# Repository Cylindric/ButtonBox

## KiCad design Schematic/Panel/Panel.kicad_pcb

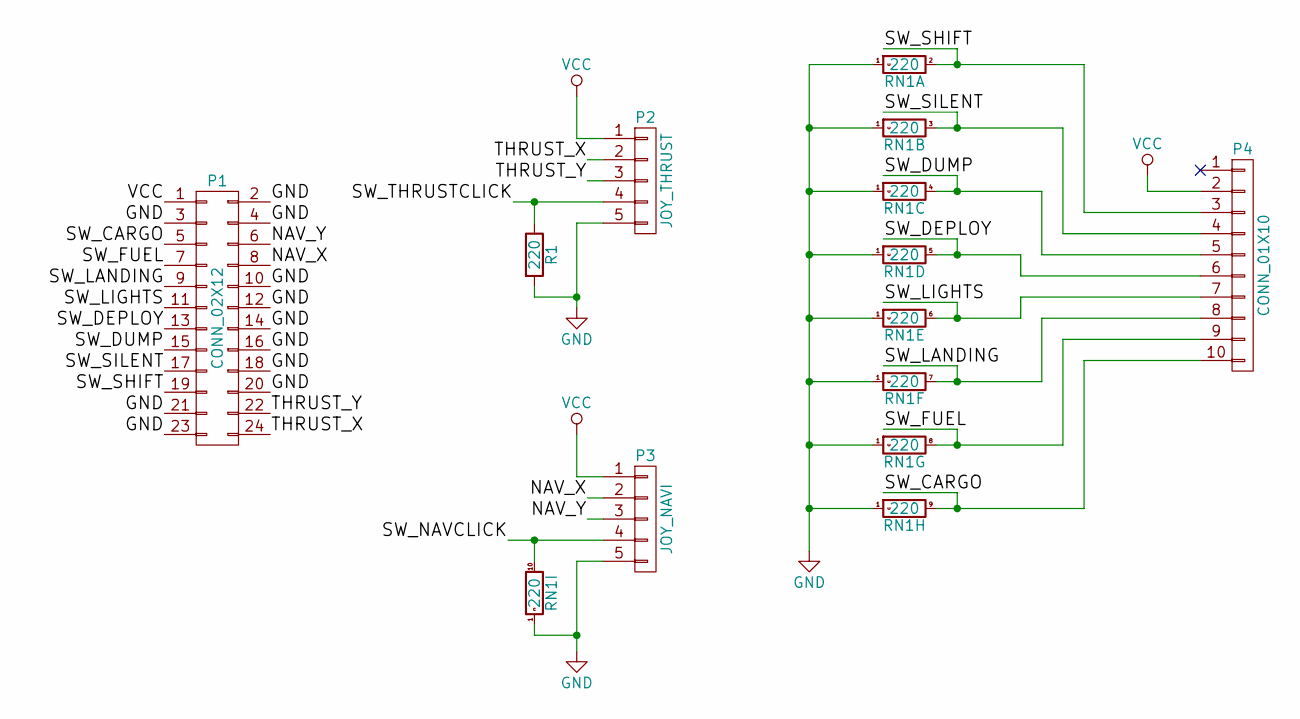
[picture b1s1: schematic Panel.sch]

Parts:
P1: CONN_02X12; Pin_Header_Straight_2x12
P2: JOY_THRUST; Pin_Header_Straight_1x05
P3: JOY_NAVI; Pin_Header_Straight_1x05
P4: CONN_01X10; Pin_Header_Straight_1x10
R1: 220; Resistor_Horizontal_RM10mm
RN1: 220; Resistor_Array_SIP9

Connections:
/NAV_X: P1.8, P3.2
/NAV_Y: P1.6, P3.3
/SW_CARGO: P1.5, P4.10, RN1.9
/SW_DEPLOY: P1.13, P4.6, RN1.5
/SW_DUMP: P1.15, P4.5, RN1.4
/SW_FUEL: P1.7, P4.9, RN1.8
/SW_LANDING: P1.9, P4.8, RN1.7
/SW_LIGHTS: P1.11, P4.7, RN1.6
/SW_NAVCLICK: P3.4, RN1.10
/SW_SHIFT: P1.19, P4.3, RN1.2
/SW_SILENT: P1.17, P4.4, RN1.3
/SW_THRUSTCLICK: P2.4, R1.1
/THRUST_X: P1.24, P2.2
/THRUST_Y: P1.22, P2.3
GND: P1.2, P1.3, P1.4, P1.10, P1.12, P1.14, P1.16, P1.18, P1.20, P1.21, P1.23, P2.5, P3.5, R1.2, RN1.1
VCC: P1.1, P2.1, P3.1, P4.2

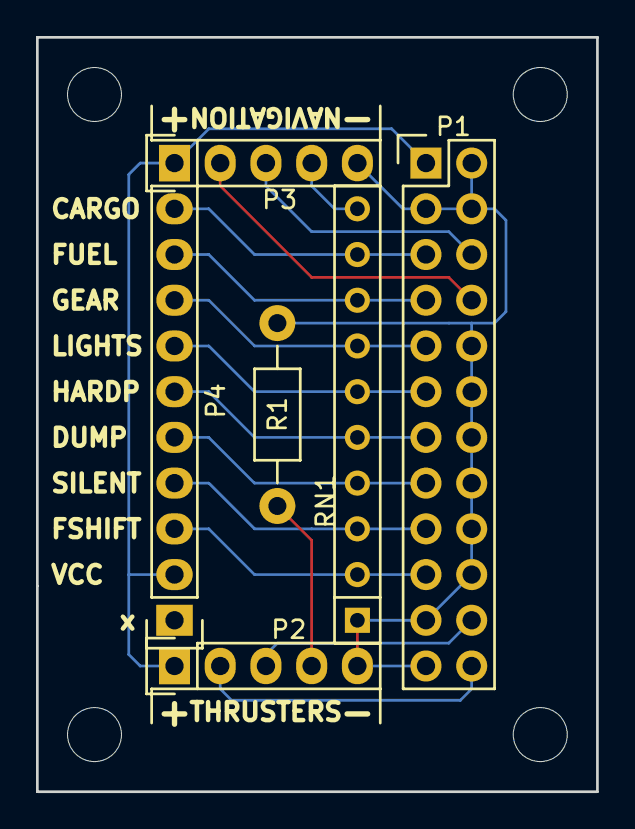
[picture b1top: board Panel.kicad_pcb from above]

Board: 2 copper layers, 31.1 x 41.9 mm, 6 parts (0 on the bottom side), 16 nets.

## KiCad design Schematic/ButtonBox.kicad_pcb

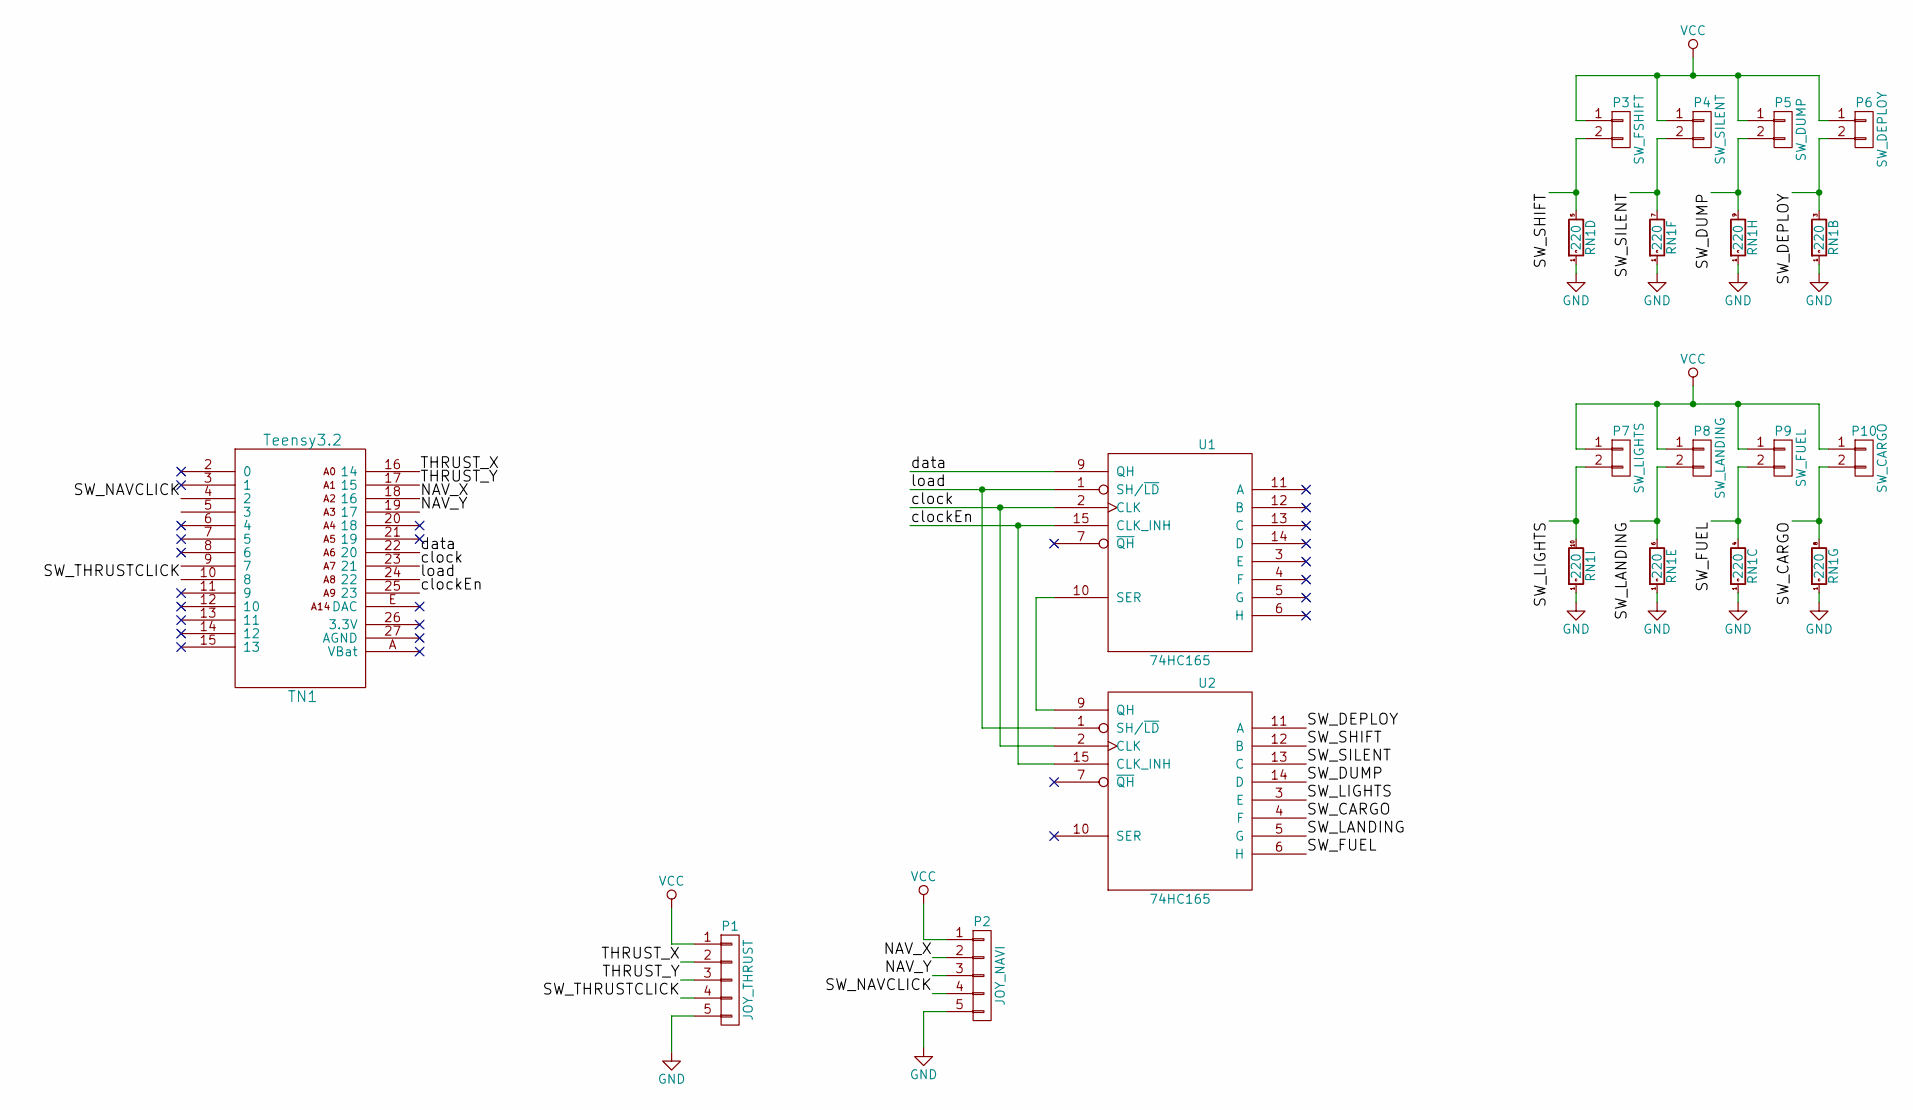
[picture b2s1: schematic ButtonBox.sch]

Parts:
P1: JOY_THRUST; Pin_Header_Angled_1x05
P2: JOY_NAVI; Pin_Header_Angled_1x05
P3: SW_FSHIFT; Pin_Header_Angled_1x02
P4: SW_SILENT; Pin_Header_Angled_1x02
P5: SW_DUMP; Pin_Header_Angled_1x02
P6: SW_DEPLOY; Pin_Header_Angled_1x02
P7: SW_LIGHTS; Pin_Header_Angled_1x02
P8: SW_LANDING; Pin_Header_Angled_1x02
P9: SW_FUEL; Pin_Header_Angled_1x02
P10: SW_CARGO; Pin_Header_Angled_1x02
RN1: 220; Resistor_Array_SIP9
TN1: Teensy3.2; Teensy
U1, U2: 74HC165; DIP-16_W7.62mm

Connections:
/NAV_X: P2.2, TN1.18 (16)
/NAV_Y: P2.3, TN1.19 (17)
/SW_CARGO: P10.2, RN1.8, U2.4 (F)
/SW_DEPLOY: P6.2, RN1.3, U2.11 (A)
/SW_DUMP: P5.2, RN1.9, U2.14 (D)
/SW_FUEL: P9.2, RN1.4, U2.6 (H)
/SW_LANDING: P8.2, RN1.6, U2.5 (G)
/SW_LIGHTS: P7.2, RN1.10, U2.3 (E)
/SW_NAVCLICK: P2.4, TN1.4 (2)
/SW_SHIFT: P3.2, RN1.5, U2.12 (B)
/SW_SILENT: P4.2, RN1.7, U2.13 (C)
/SW_THRUSTCLICK: P1.4, TN1.10 (8)
/THRUST_X: P1.2, TN1.16 (14)
/THRUST_Y: P1.3, TN1.17 (15)
/clock: TN1.23 (21), U1.2 (CLK), U2.2 (CLK)
/clockEn: TN1.25 (23), U1.15 (CLK_INH), U2.15 (CLK_INH)
/data: TN1.22 (20), U1.9 (QH)
/load: TN1.24 (22), U1.1 (SH/~LD), U2.1 (SH/~LD)
GND: P1.5, P2.5, RN1.1, TN1.1 (GND), TN1.C (GND), U1.8 (GND), U2.8 (GND)
unnamed: U1.10 (SER), U2.9 (QH)
VCC: P1.1, P2.1, P3.1, P4.1, P5.1, P6.1, P7.1, P8.1, P9.1, P10.1, U1.16 (VCC), U2.16 (VCC)

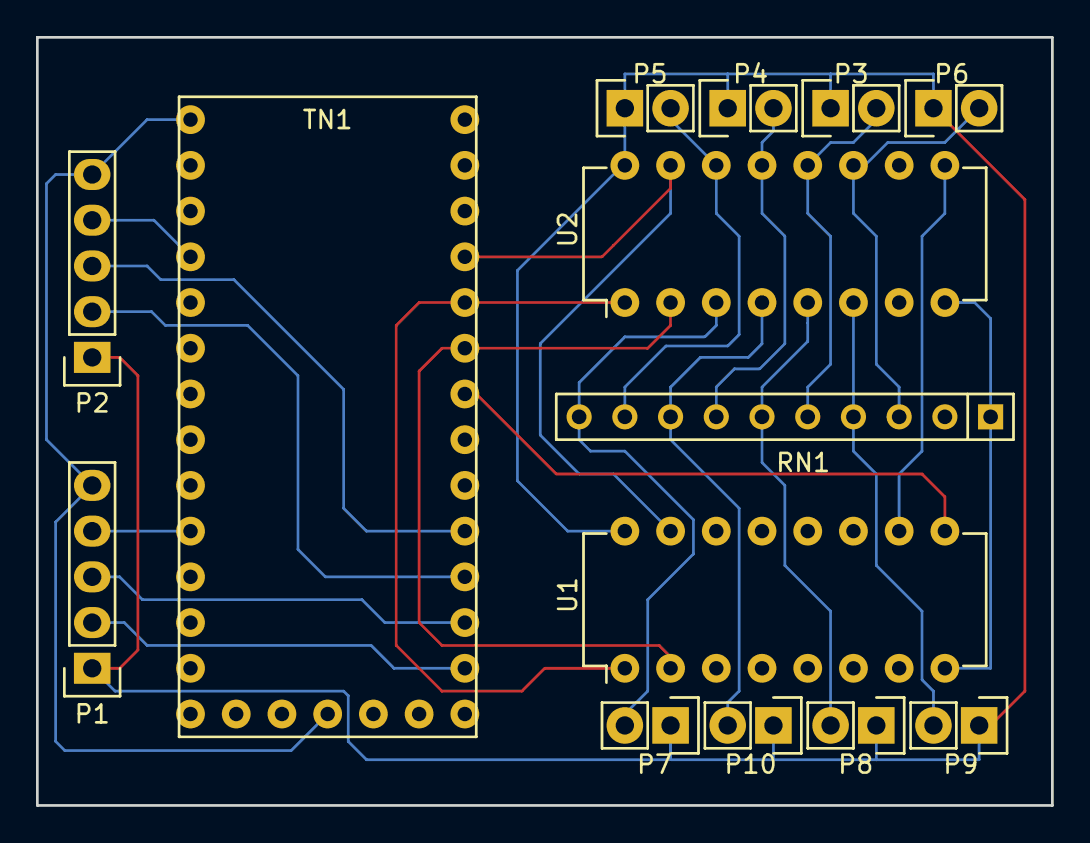
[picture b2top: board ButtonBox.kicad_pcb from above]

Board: 2 copper layers, 56.4 x 42.7 mm, 14 parts (0 on the bottom side), 21 nets.

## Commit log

2015-12-27 More work on v1 schematic and board layout.
2015-12-27 Single board design.
2015-12-27 Split controller and button interfance.
